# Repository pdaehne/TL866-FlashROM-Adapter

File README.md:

# TL866 FlashROM Programming Adapter

This repository contains the KiCad project and Gerber files for a TL866
Programming Adapter for 29F400/29F800/29F160 Flash ROMs which are used to
replace 29C400/29C800/29C160 EPROMs in retro machines like the Amiga.

> [!IMPORTANT]
> Besides this adapter, you also need the SN001-1 TSOP48 adapter which came with your
> TL866 or which is sold separately!

> [!WARNING]
> I use this adapter with my TL866 II plus. I do not know if it works with the
> older TL866 A or CS, but it probably does. It does __not__ work with the newer
> Xgecu T48 aka TL866-3G or the Xgecu T56 programmers!

## Ordering the PCB

The subdirectory "gerber-files" contains a Zip file you can use to order the PCB
from PCB manufacturers like PCBWay or JLCPCB. Simply upload the Zip on their web
page. I recommend to order the standard PCB thickness of 1.6mm and HASL
finishing.

## Building the Adapter

### Bill of Materials

* __1x ZIF Socket 48 Pins 2.54mm pitch__

  This is where you put the Flash ROM into.

* __2x 2x12 Female Pin Sockets Through Hole Straight Angle 2.54mm pitch__

  Used to connect this adapter to the SN-001-01 adapter.

* __1x 2x3 Male Pin Header Through Hole Straight Angle 2.54mm pitch__

  There are some signals on this pin header that you need to connect to your
  Flash ROM.

* __Dupont Jumper cables depending on your type of Flash ROM__

  These are used to connect the signals on the pin header to your Flash ROM.
  This depends on your type of Flash ROM. For my Flash ROM, five short
  female-to-female jumper cables are needed.

### Soldering the ZIF Socket

Insert the ZIF socket into the PCB. This can be a little bit fiddly, because the
quality of the cheap ZIF sockets from Aliexpress is quite low, the pins are
usually bend and the holes in the PCB are small. You might have to use pliers to
bend the pins in shape, but do not bend to much, otherwise the parts on the top
side of the ZIF socket might start moving and get out of alignment. Solder the
socket from the bottom side.

### Soldering the Connection to the SN001-1 Adapter

Next, solder the two 2x12 pin headers to the underside of the PCB which connect
the PCB to the SN001-1 adapter. It is crucial that these pin headers are
correctly aligned, otherwise they might not fit onto the adapter. I recommend to
stick the SN001-1 adapter into a breadboard, stick the 2x12 pin headers onto
the adapter, and finally put the PCB on the pin headers. Doing so ensures
correct alignment, but you have to be careful not to drop solder onto the
SN001-1 adapter or the breadboard.

### Soldering the 2x3 Pin Headers

Finally, solder the 2x3 pin headers onto the PCB. This is a simple and
straightforward task.

## Where to get a Flash ROM

You can use the following projects to order PCBs for the Flash ROM, but keep in
mind that the flash chips are SMD parts (TSOP48) which are not easy to solder:

* A KiCad Project:

  https://gitlab.com/rwahler1/kicad/Amiga_27C400_Emulator2/

* Another project (Gerbers only):

  https://github.com/OlegMishin/FlashROM/

* A PCBWay Shared Project:

  https://www.pcbway.com/project/shareproject/Amiga_Flash_ROM_Adapter.html

You can also buy pre-built Flash ROMs, e.g. from the following shops (I do
not have any affiliation with these shops):

* Alinea (Germany):

  https://www.amiga-shop.net/Amiga-Hardware/Amiga-Kabel-Adapter/KickRom-Flash-4-fach-Flash-Rom-Adapter-27C400-Emulator::1305.html

* AMIGAstore.eu (Spain)

  https://amigastore.eu/en/826-dual-kickstart-rom-flash-adapter-switcher-.html

* Retro Rewind (Canada)

  https://retrorewind.ca/amiga-flashrom-8mbit

## Using the Adapter

First, put the adapter on top of the SN001-1 adapter. Then, put both adapters
into the TL866 ZIF socket. Put your Flash ROM into the ZIF socket of
the adapter. __Your Flash ROM needs to be aligned to the bottom of the ZIF
socket!!!__.

The final step is to connect a few signals which are available on the 2x3 pin
header on the top left of the PCB to your Flash ROM by using Dupont jumper wires
like the ones used for breadboards. This depends a little bit on the type of
Flash ROM you are using.

On the right side of the 2x3 pin header are the signals RDY ("Ready",
sometimes also called /BSY or "Busy"), /RST ("Reset"), and /WE ("Write Enable").
These are needed on all types of Flash ROMs. Locate these signals on your Flash
ROM, and connect them to the pin header using jumper wires.

On the left side of the 2x3 pin header are the address lines A18 and A19.
Connecting these depends on the type of Flash ROM you have. Usually, these are
the pins where you connect a switch to be able to select between different
ROMs.

When you're using a 40 pin Flash ROM for 16 bit machines like the Amiga 500,
you have to connect the address lines like this:

* When you have a 29F400 flash, you do not need to connect the address lines
  at all.

* When you have a 29F800 flash, you have to connect the address line A18.
  Locate that signal on your Flash ROM, and connect it to the pin header using
  a jumper wire.

* When you have a 29F160 flash, you have to connect both address lines A18 and
  A19. Locate these signals on your Flash ROM, and connect them to the pin
  header using jumper wires.

When you're using a 42 pin Flash ROM for 32 bit machines like the Amiga 1200,
you do not need to connect these address lines at all. They are already
connected by the top two pins in the ZIF socket.

The image below shows my 40 pin Flash ROM designed by Matthias Münch with a
29F160 flash with all jumper cables attached. Your Flash ROM might look a little
bit different.

When everything is set up correctly, you can connect the TL866 to the USB port
of your computer and start programming the flash.

I do have a 29F160 Flash ROM for my Amiga 500, which has a capacity of 2
megabytes or 4 slots of 512 kilobytes for different Kickstart ROMs. I wanted to
have the original Kickstart 1.3 in the first slot, Kickstart 3.1 in the second
slot, the [Diagnostic ROM](https://www.diagrom.com/) in the third slot, and the
fourth slot unused.

To program the flash, you can use the original "Xgpro" software which came with
the TL866 on Windows, or the
[opensource software "minipro"](https://gitlab.com/DavidGriffith/minipro) on
MacOS or Linux. In the following two sections, I will explain both ways to
program the Flash ROM.

### Using the original "Xgpro" software on Windows

After starting the "Xgpro" software, you first have to select the correct
Flash chip that is soldered on your Flash ROM. On my Flash ROM, it is a
M29F160FB, but on your Flash ROM it might be a different flash chip. Have a
look at what is written on your flash chip.

After selecting the correct flash chip, we have to fill the data buffer with the
data we want to write onto the flash. The data buffer by default is shown in the
program window as 16 bit words filled with hexadecimal $FFFF, and the addresses
shown on the left side are word addresses. Because this can be confusing, I
recommend to switch the buffer view to "8 Bits".

In the first slot (addresses $000000-$07FFFF) we want to write the Kickstart
1.3 ROM. But there is one little problem: Each slot has 512 kilobytes, but the
Kickstart 1.3 ROM is only 256 kilobytes. What you have to do is to copy the
Kickstart 1.3 ROM __twice__ into the final ROM file. So in the Xgpro Software,
click on "LOAD". In the "File load Options" dialog, click on "Browse"
and select the Kickstart 1.3 ROM file. "File Format" must be "BINARY". The
"Load mode" must be "Normal", "From File Start Addr(Hex)" must be "00000", and
"TO Buffer Strat Addr(HEX)" must be "00000". "Clear Buffer when loading the
file" must be set to "Disable". After clicking "OK", the buffer gets filled with
Kickstart 1.3 from addresses $000000-$3FFFF. Now, click on "LOAD" again, and
this time load the Kickstart 1.3 ROM file to buffer start address "40000". All
other settings stay the same. Do not forget to disable "Clear Buffer"!

In the second slot (addresses $080000-$0fffff) we want to write the Kickstart
3.1 ROM. So click on "LOAD" again and click on "Browse" to select the Kickstart
3.1 ROM file. Set the buffer start address to "80000", and set all other options
as for the 1.3 ROM. Again, do not forget to disable "Clear Buffer"!

In the third slot (addresses $100000-$17ffff) we want to write the diagnostic
ROM. So click on "LOAD" and on "Browse" to select the diagnostic ROM file. Set
the buffer start address to "100000", and set all other options as for the
previous ROMs. Do not forget to disable "Clear Buffer"!

Now we are almost finished, but there is one more important step to do: We have
to swap the bytes of the two Kickstart ROMs because the Motorola 68000 is a big
endian machine, and the machine used for burning the flash is a little endian
machine. The diagnostic ROM already is byte swapped! Click on the menu entry
"File(F)/Fill Block/Swap(F)". In the "Fill block" dialog, make sure
"Stard_Addr: 0x" is set to "00000000", and set "End_Addr: 0x" to "000fffff".
Under "Swap Byte or Word", select "16Bits" and click on the "Swap" button.

Now we are finally ready to program the flash chip!

### Using the opensource software "minipro" on MacOS and Linux

First of all, you have to byte swap the Kickstart ROMs, because the Motorola
68000 is a big endian machine, and the machine used for burning the flash is a
little endian machine. To do that, we can use the "dd" command like this:

```
dd if=Kickstart1.3.rom of=Kickstart1.3.swapped.rom conv=swab
dd if=Kickstart3.1.rom of=Kickstart3.1.swapped.rom conv=swab
```

The diagnostic ROM already is byte swapped, so we can use it directly. Now we
have to combine the ROMs into one single file. But there is one little problem:
Each slot has 512 kilobytes, but the Kickstart 1.3 ROM is only 256 kilobytes.
What you have to do is to copy the Kickstart 1.3 ROM __twice__ into the final
ROM file. To create the final combined file, I use the "cat" command like this:

```
cat Kickstart1.3.swapped.rom Kickstart1.3.swapped.rom Kickstart3.1.swapped.rom 16bit.bin >combined.rom
```

This file is 512 kilobytes too small, but that does not matter.

Finally, I use the "minipro" command to burn the ROM file to the flash:

```
minipro -p "M29F160FB@TSOP48" -s -w combined.rom
```

The "-p" option specifies the type of flash that is soldered on your Flash ROM.
On my Flash ROM, it is a M29F160FB, but on your Flash ROM it might be a
different flash chip. Have a look at what is written on your flash chip, and
adjust the "-p" option accordingly. The "-s" option tells the minipro command
that our file does not fill the complete flash, and the "-w" option tells the
minipro command to write the file "combined.rom" to the flash.

## License

TL866 FlashROM Programming Adapter (c) by Patrick Dähne

TL866 FlashROM Programming Adapter is licensed under a
Creative Commons Attribution-NonCommercial-ShareAlike 4.0 International License.

You should have received a copy of the license along with this
work. If not, see <https://creativecommons.org/licenses/by-nc-sa/4.0/>.

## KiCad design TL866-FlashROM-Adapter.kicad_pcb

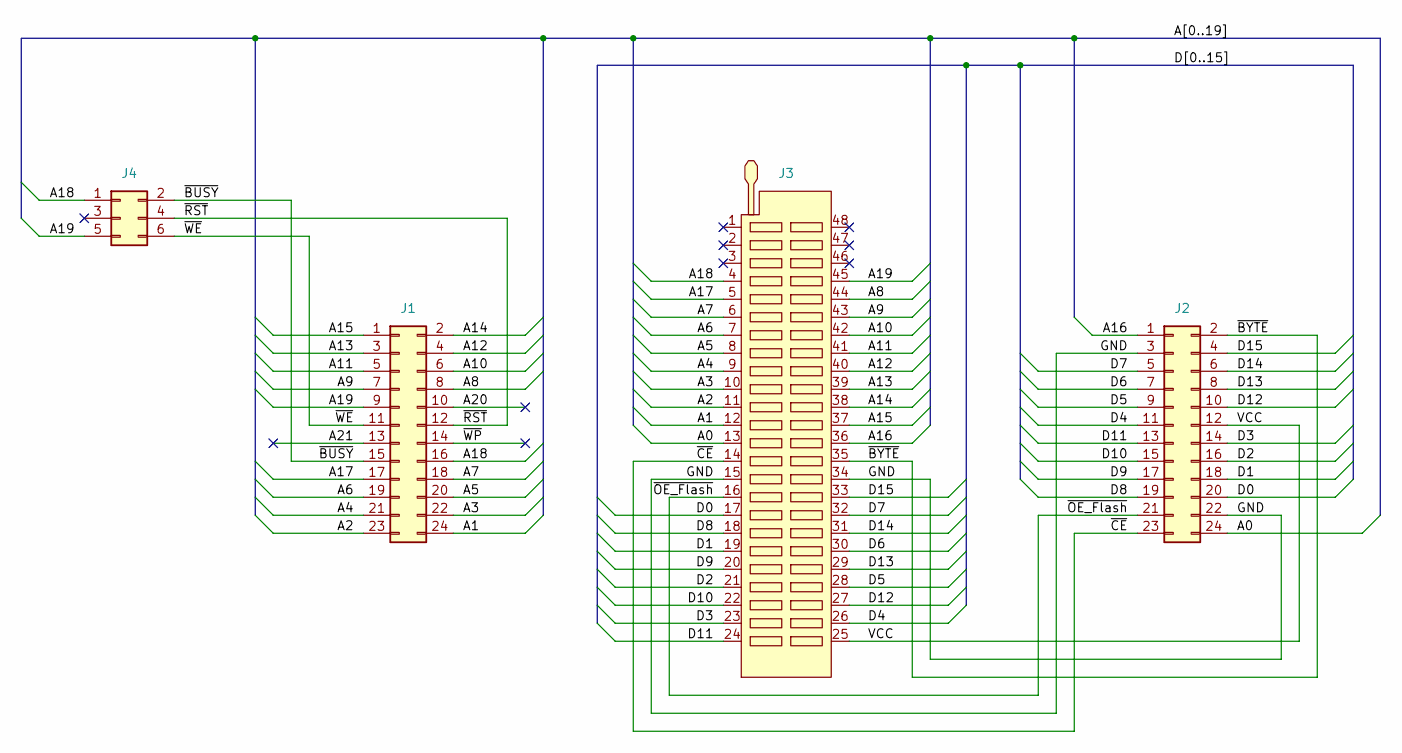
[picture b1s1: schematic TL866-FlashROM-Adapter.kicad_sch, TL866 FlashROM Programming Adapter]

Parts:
J1, J2: Conn_02x12_Odd_Even; PinSocket_2x12_P2.54mm_Vertical
J3: ZIF_48Pin
J4: Conn_02x03_Odd_Even; PinHeader_2x03_P2.54mm_Vertical

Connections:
/A0: J2.24, J3.13
/A1: J1.24, J3.12
/A2: J1.23, J3.11
/A3: J1.22, J3.10
/A4: J1.21, J3.9
/A5: J1.20, J3.8
/A6: J1.19, J3.7
/A7: J1.18, J3.6
/A8: J1.8, J3.44
/A9: J1.7, J3.43
/A10: J1.6, J3.42
/A11: J1.5, J3.41
/A12: J1.4, J3.40
/A13: J1.3, J3.39
/A14: J1.2, J3.38
/A15: J1.1, J3.37
/A16: J2.1, J3.36
/A17: J1.17, J3.5
/A18: J1.16, J3.4, J4.1
/A19: J1.9, J3.45, J4.5
/A20: J1.10
/A21: J1.13
/D0: J2.20, J3.17
/D1: J2.18, J3.19
/D2: J2.16, J3.21
/D3: J2.14, J3.23
/D4: J2.11, J3.26
/D5: J2.9, J3.28
/D6: J2.7, J3.30
/D7: J2.5, J3.32
/D8: J2.19, J3.18
/D9: J2.17, J3.20
/D10: J2.15, J3.22
/D11: J2.13, J3.24
/D12: J2.10, J3.27
/D13: J2.8, J3.29
/D14: J2.6, J3.31
/D15: J2.4, J3.33
/GND: J2.3, J2.22, J3.15, J3.34
/VCC: J2.12, J3.25
/~BUSY: J1.15, J4.2
/~BYTE: J2.2, J3.35
/~CE: J2.23, J3.14
/~OE_Flash: J2.21, J3.16
/~RST: J1.12, J4.4
/~WE: J1.11, J4.6
/~WP: J1.14

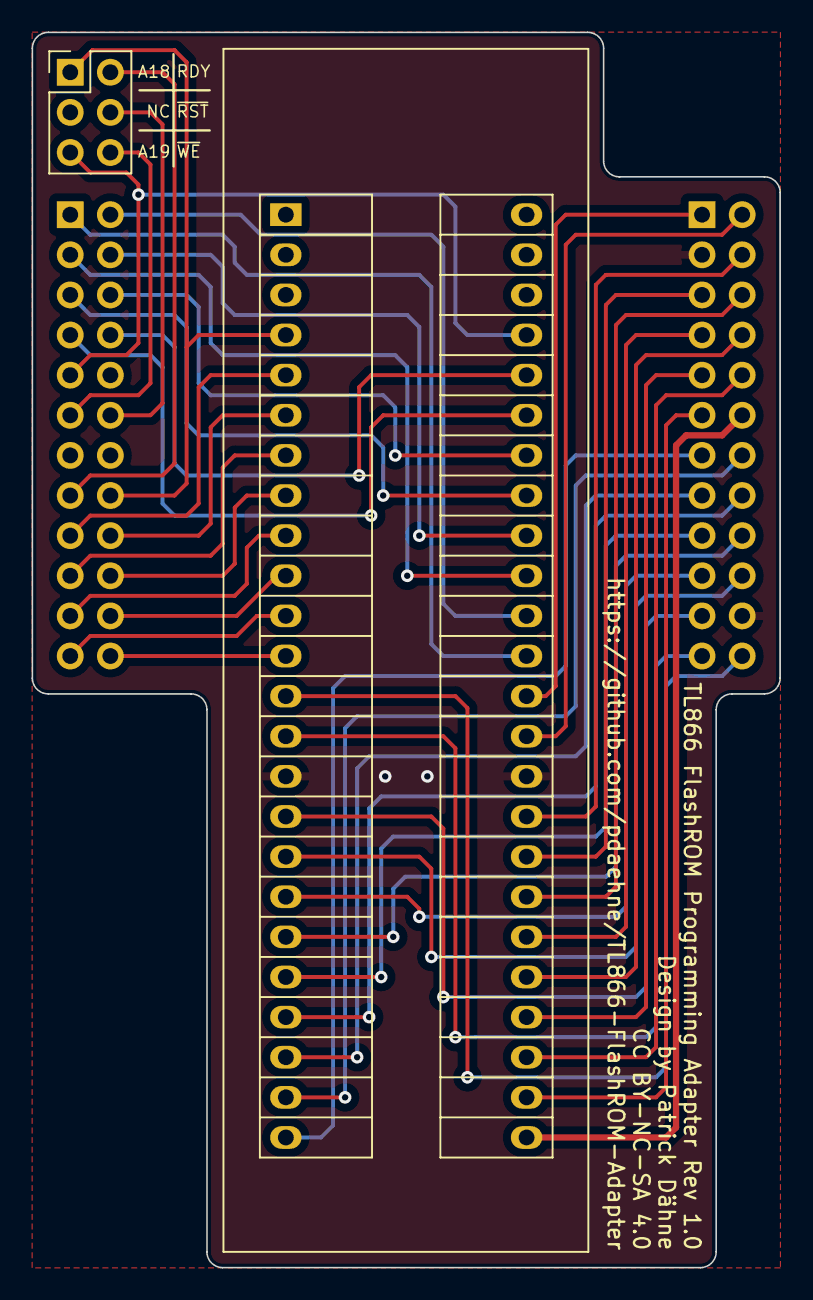
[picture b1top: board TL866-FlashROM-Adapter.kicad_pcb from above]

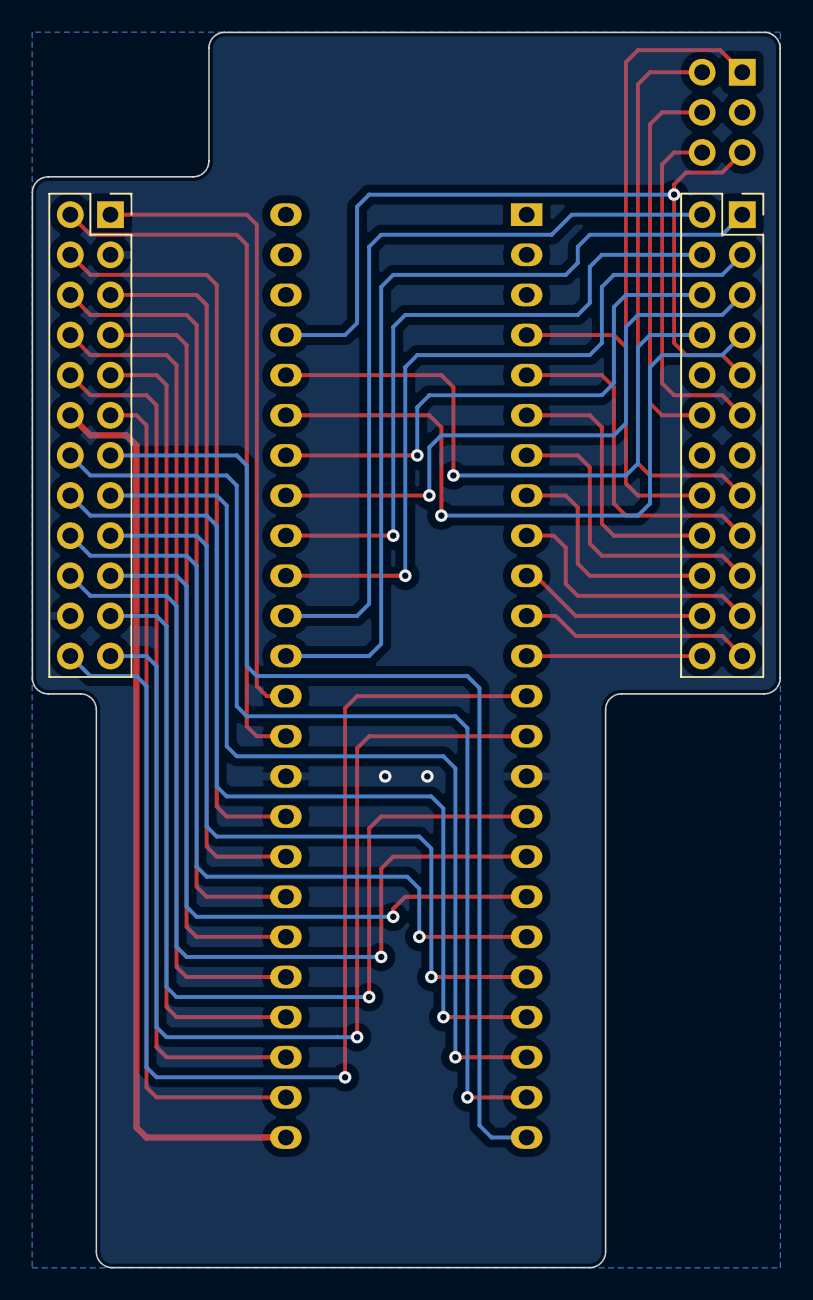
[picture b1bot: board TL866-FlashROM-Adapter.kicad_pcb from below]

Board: 2 copper layers, 47.3 x 78.2 mm, 4 parts (2 on the bottom side), 44 nets.

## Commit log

2024-03-08 Initial check-in
2024-03-08 Added readme file
2024-08-22 Added documentation for the Xgpro software
2024-08-22 Fixed typo
2024-09-20 Added picture of pin assignment
2024-09-23 Improved README
2024-09-28 Added section about where to get Flash ROMs
2024-10-10 Removed alpha channel
2025-01-20 Fixed access rights
2025-12-03 Added recommendation for PCB thickness and finishing, fixed a typo
2025-12-03 Replaced one word

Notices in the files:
TL866-FlashROM-Adapter.kicad_pcb:
Patrick Dähne CC BY-NC-SA 4.0
CC BY-NC-SA 4.0
